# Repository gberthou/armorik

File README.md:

# ARMorik

This project proposes a simple platform that interfaces an ARM-based micro-controller (ATSAMS70, Cortex-M7-based) and non-volatile ferroelectric memory,
as an alternative to TI's MSP430FR series.

Industry lacks micro-controllers equipped with non-volatile RAM (NVRAM).
The only existing micro-controllers equipped with NVRAM have small RAM and NVRAM memories, not larger than a few kilobytes.
There is a need for micro-controllers with bigger RAM and NVRAM, implementing other architectures as well, such as ARM.

If such platforms do not exist yet, why not build one ourselves?
Here, the idea is quite simple:
take an ARM-based micro-controller which provides external pins for External Bus Interface (EBI) and which provides a Static Memory Controller (SMC).

## Hardware

- MCU: [ATSAMS70Q19](https://www.microchip.com/wwwproducts/en/ATSAMS70Q19) (ARM Cortex-M7)
- NVRAM: [FM28V202A](https://www.cypress.com/part/fm28v202a-tg) (256kB ferroelectric NVRAM)
- Socket for a [CC2500EMK](https://www.ti.com/tool/CC2500EMK) module
- [ADT7310](https://www.analog.com/en/products/adt7310.html) SPI temperature sensor
- NSL-4962 photoresistor

## Power supply

The platform is powered by a simple USB Micro-B cable.
With the onboard switch, you can choose whether you want to use the 2.2V supply or the variable supply.
The latter can be configured between 2V and 3.3V by using the onboard potentiometer.

## Programming

The platform embeds a socket for the SWD interface.
It was tested with the [Atmel ICE](https://www.microchip.com/DevelopmentTools/ProductDetails/ATATMEL-ICE) programmer.

## Code samples

My other project, [sytARM](https://gitlab.inria.fr/gabertho/sytarm), shows code and the required toolchain to make this code run on the ARMorik platform.

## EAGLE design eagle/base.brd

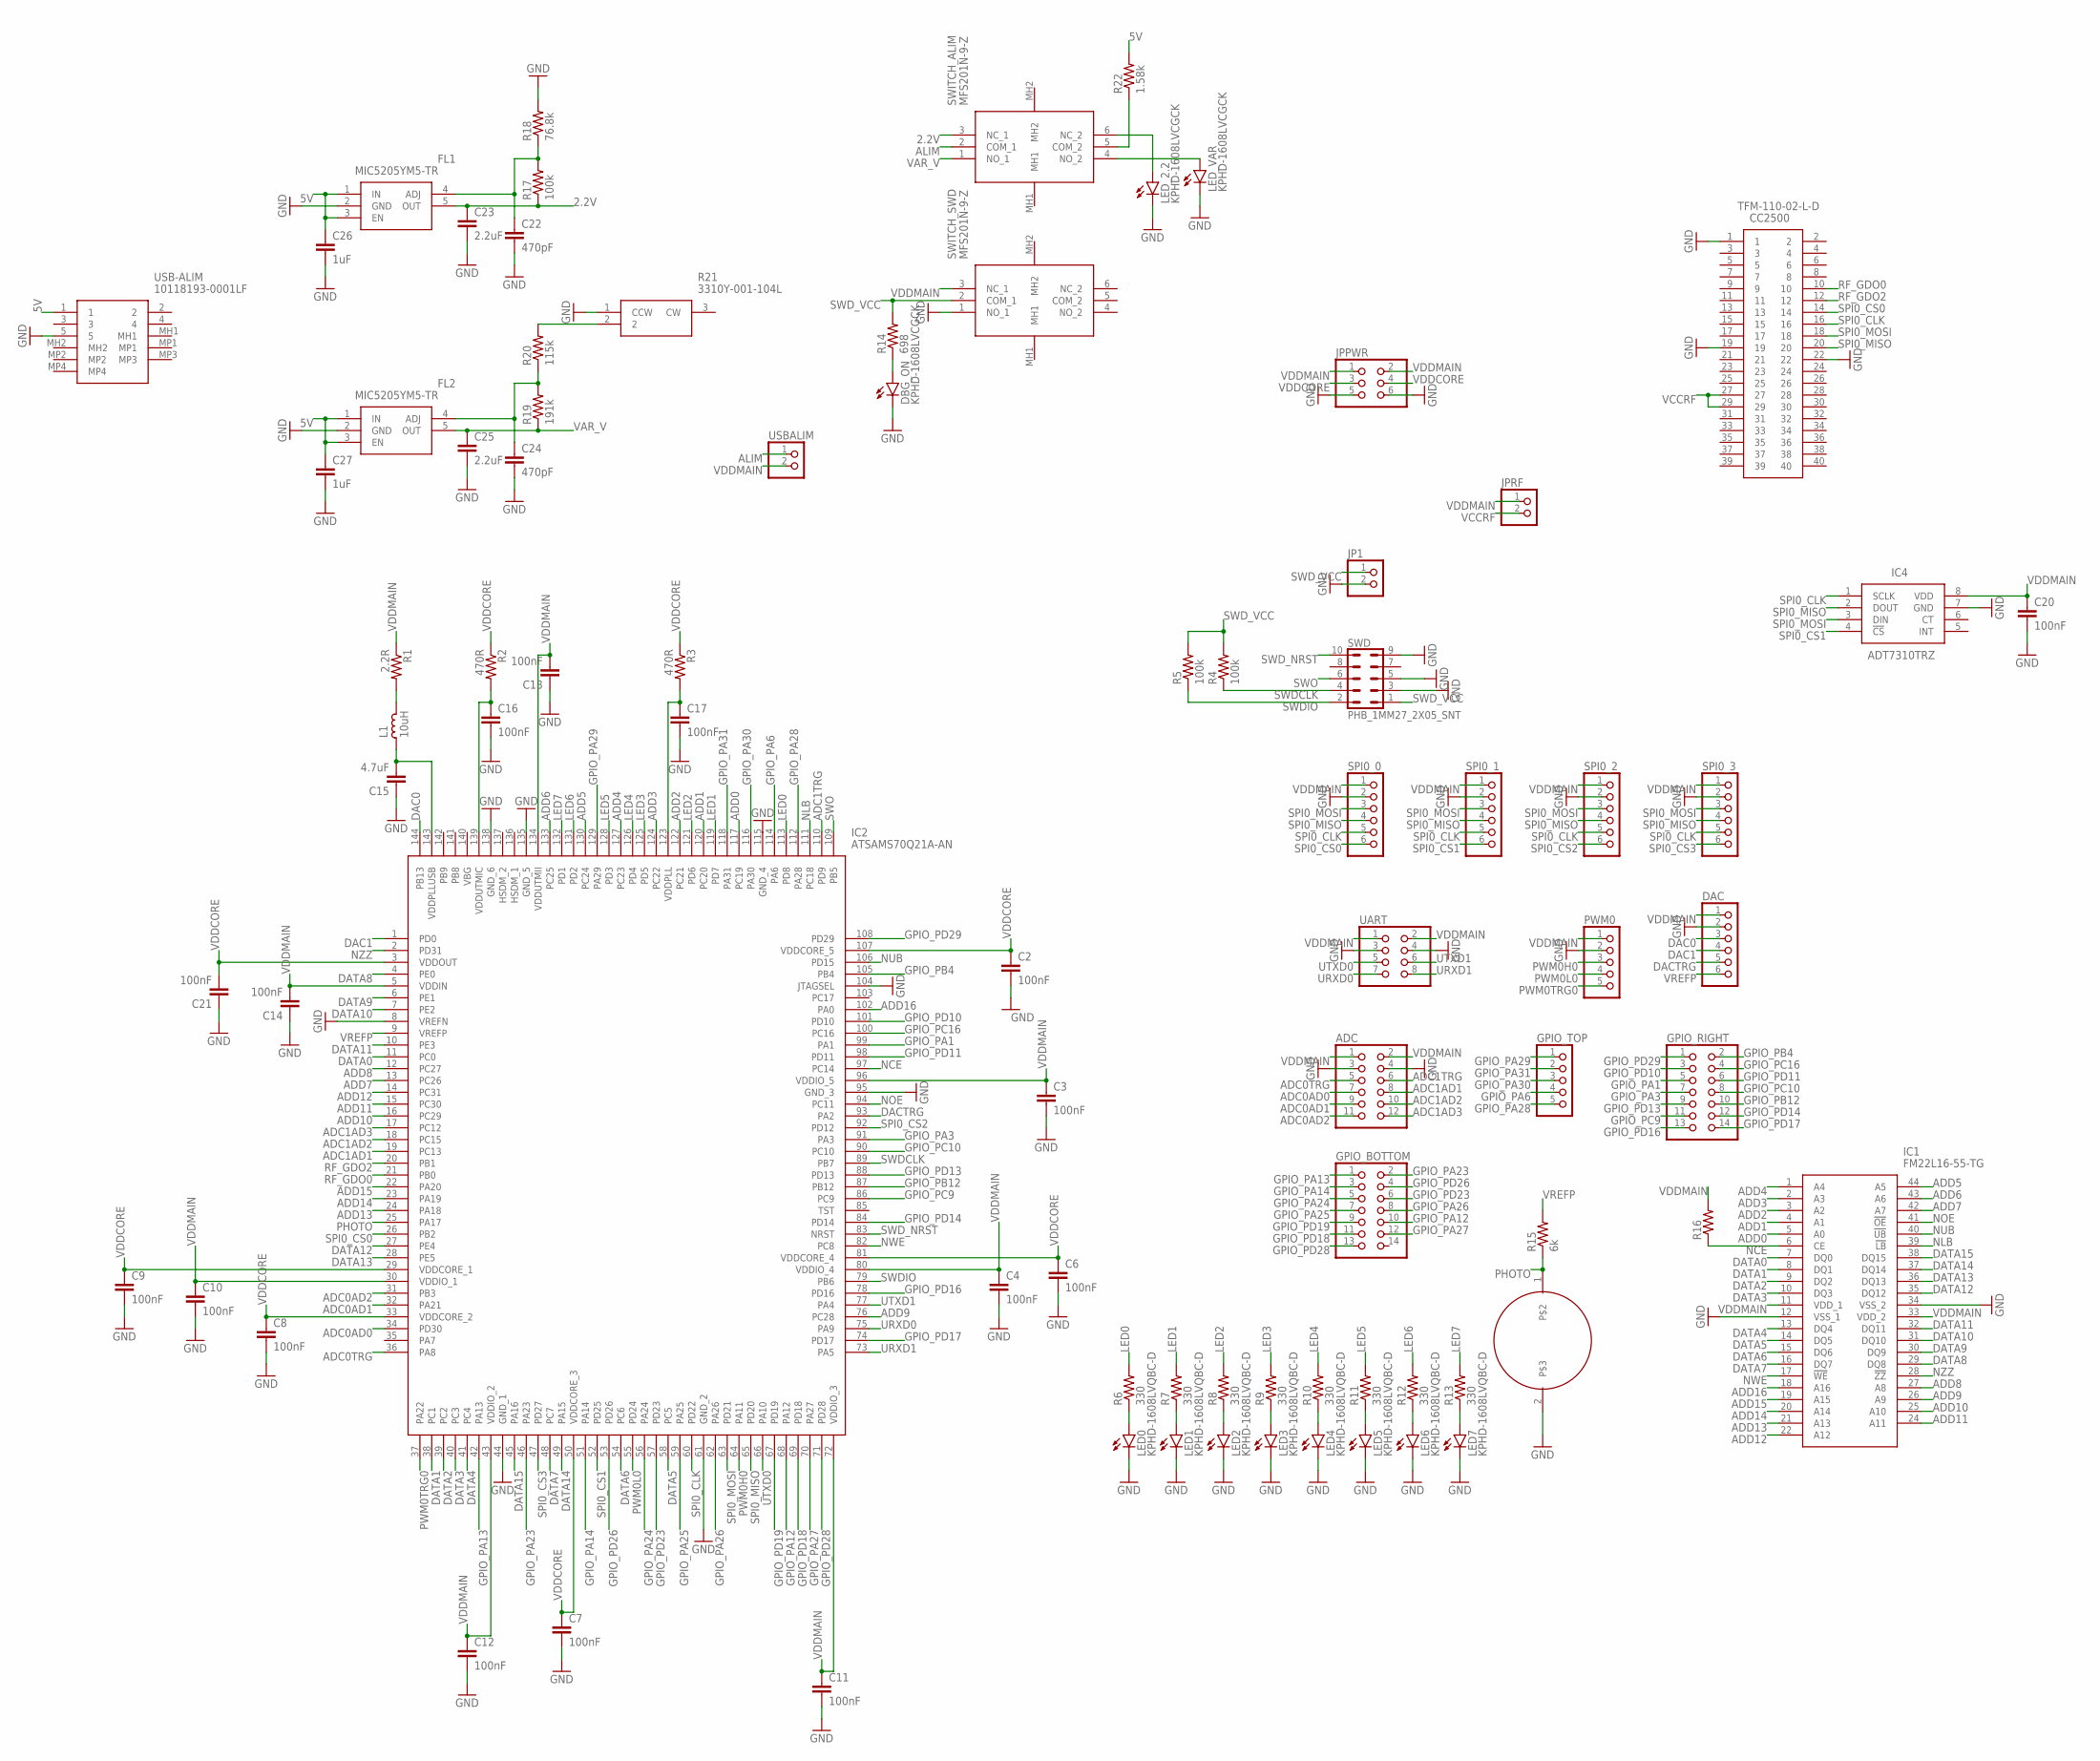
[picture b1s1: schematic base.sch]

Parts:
ADC: PINHD-2X6; 2X06
C2, C3, C4, C6, C7, C8, C9, C10, C11, C12, C13, C14, C16, C17, C20, C21: 100nF; C0603
C15: 4.7uF; C0603
C22, C24: 470pF; C0603
C23, C25: 2.2uF; C0603
C26, C27: 1uF; C0603
CC2500: TFM-110-02-L-D; TFM-110-02-L
DAC: PINHD-1X6; 1X06
DBG_ON: KPHD-1608LVCGCK; CHIP-LED0603
FL1, FL2: MIC5205YM5-TR; SOT95P280X145-5N
GPIO_BOTTOM: PINHD-2X7; 2X07
GPIO_RIGHT: PINHD-2X7; 2X07
GPIO_TOP: PINHD-1X5; 1X05
IC1: FM22L16-55-TG; SOP80P1184X119-44N
IC2: ATSAMS70Q21A-AN; QFP50P2200X2200X160-144N
IC4: ADT7310TRZ; SOIC127P600X175-8N
JP1: PINHD-1X2; 1X02
JPPWR: PINHD-2X3; 2X03
JPRF: PINHD-1X2; 1X02
L1: 10uH; L0603
LED0, LED1, LED2, LED3, LED4, LED5, LED6, LED7: KPHD-1608LVQBC-D; CHIP-LED0603
LED_2.2: KPHD-1608LVCGCK; CHIP-LED0603
LED_VAR: KPHD-1608LVCGCK; CHIP-LED0603
PWM0: PINHD-1X5; 1X05
R1: 2.2R; R0603
R2, R3: 470R; R0603
R4, R5, R17: 100k; R0603
R6, R7, R8, R9, R10, R11, R12, R13: 330; R0603
R14: 698; R0603
R15: 6k; R0603
R16: R-US_R0603; R0603
R18: 76.8k; R0603
R19: 191k; R0603
R20: 115k; R0603
R21: 3310Y-001-104L; 3310Y-001
R22: 1.58k; R0603
SPI0_0, SPI0_1, SPI0_2, SPI0_3: PINHD-1X6; 1X06
SWD: PHB_1MM27_2X05_SNT
SWITCH_ALIM: MFS201N-9-Z; MFS201N9Z
SWITCH_SWD: MFS201N-9-Z; MFS201N9Z
U$1: NSL-4962; TO-8
UART: PINHD-2X4; 2X04
USB-ALIM: 10118193-0001LF; 101181930001LF
USBALIM: PINHD-1X2; 1X02

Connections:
2.2V: C23.1, FL1.5 (OUT), R17.1, SWITCH_ALIM.3 (NC_1)
5V: C26.1, C27.1, FL1.1 (IN), FL1.3 (EN), FL2.1 (IN), FL2.3 (EN), R22.2, USB-ALIM.1
ADC0AD0: ADC.7, IC2.34 (PD30)
ADC0AD1: ADC.9, IC2.32 (PA21)
ADC0AD2: ADC.11, IC2.31 (PB3)
ADC0TRG: ADC.5, IC2.36 (PA8)
ADC1AD1: ADC.8, IC2.19 (PC13)
ADC1AD2: ADC.10, IC2.18 (PC15)
ADC1AD3: ADC.12, IC2.17 (PC12)
ADC1TRG: ADC.6, IC2.110 (PD9)
ADD0: IC1.5 (A0), IC2.117 (PC19)
ADD1: IC1.4 (A1), IC2.120 (PC20)
ADD2: IC1.3 (A2), IC2.122 (PC21)
ADD3: IC1.2 (A3), IC2.124 (PC22)
ADD4: IC1.1 (A4), IC2.127 (PC23)
ADD5: IC1.44 (A5), IC2.130 (PC24)
ADD6: IC1.43 (A6), IC2.133 (PC25)
ADD7: IC1.42 (A7), IC2.13 (PC26)
ADD8: IC1.27 (A8), IC2.12 (PC27)
ADD9: IC1.26 (A9), IC2.76 (PC28)
ADD10: IC1.25 (A10), IC2.16 (PC29)
ADD11: IC1.24 (A11), IC2.15 (PC30)
ADD12: IC1.22 (A12), IC2.14 (PC31)
ADD13: IC1.21 (A13), IC2.24 (PA18)
ADD14: IC1.20 (A14), IC2.23 (PA19)
ADD15: IC1.19 (A15), IC2.22 (PA20)
ADD16: IC1.18 (A16), IC2.102 (PA0)
ALIM: SWITCH_ALIM.2 (COM_1), USBALIM.1
DAC0: DAC.3, IC2.144 (PB13)
DAC1: DAC.4, IC2.1 (PD0)
DACTRG: DAC.5, IC2.93 (PA2)
DATA0: IC1.7 (DQ0), IC2.11 (PC0)
DATA1: IC1.8 (DQ1), IC2.38 (PC1)
DATA2: IC1.9 (DQ2), IC2.39 (PC2)
DATA3: IC1.10 (DQ3), IC2.40 (PC3)
DATA4: IC1.13 (DQ4), IC2.41 (PC4)
DATA5: IC1.14 (DQ5), IC2.58 (PC5)
DATA6: IC1.15 (DQ6), IC2.54 (PC6)
DATA7: IC1.16 (DQ7), IC2.48 (PC7)
DATA8: IC1.29 (DQ8), IC2.4 (PE0)
DATA9: IC1.30 (DQ9), IC2.6 (PE1)
DATA10: IC1.31 (DQ10), IC2.7 (PE2)
DATA11: IC1.32 (DQ11), IC2.10 (PE3)
DATA12: IC1.35 (DQ12), IC2.27 (PE4)
DATA13: IC1.36 (DQ13), IC2.28 (PE5)
DATA14: IC1.37 (DQ14), IC2.49 (PA15)
DATA15: IC1.38 (DQ15), IC2.45 (PA16)
GND: ADC.3, ADC.4, C2.2, C3.2, C4.2, C6.2, C7.2, C8.2, C9.2, C10.2, C11.2, C12.2, C13.1, C14.1, C15.1, C16.2, C17.2, C20.2, C21.1, C22.2, C23.2, C24.2, C25.2, C26.2, C27.2, CC2500.1, CC2500.19, CC2500.22, DAC.2, DBG_ON.C, FL1.2 (GND), FL2.2 (GND), IC1.12 (VSS_1), IC1.34 (VSS_2), IC2.8 (VREFN), IC2.44 (GND_1), IC2.61 (GND_2), IC2.95 (GND_3), IC2.104 (JTAGSEL), IC2.115 (GND_4), IC2.135 (GND_5), IC2.138 (GND_6), IC4.7 (GND), JP1.2, JPPWR.5, JPPWR.6, LED0.C, LED1.C, LED2.C, LED3.C, LED4.C, LED5.C, LED6.C, LED7.C, LED_2.2.C, LED_VAR.C, PWM0.2, R18.2, R21.1 (CCW), SPI0_0.2, SPI0_1.2, SPI0_2.2, SPI0_3.2, SWD.3, SWD.5, SWD.9, SWITCH_SWD.1 (NO_1), U$1.2, UART.3, UART.4, USB-ALIM.5
GPIO_PA1: GPIO_RIGHT.5, IC2.99 (PA1)
GPIO_PA3: GPIO_RIGHT.7, IC2.91 (PA3)
GPIO_PA6: GPIO_TOP.4, IC2.114 (PA6)
GPIO_PA12: GPIO_BOTTOM.10, IC2.68 (PA12)
GPIO_PA13: GPIO_BOTTOM.1, IC2.42 (PA13)
GPIO_PA14: GPIO_BOTTOM.3, IC2.51 (PA14)
GPIO_PA23: GPIO_BOTTOM.2, IC2.46 (PA23)
GPIO_PA24: GPIO_BOTTOM.5, IC2.56 (PA24)
GPIO_PA25: GPIO_BOTTOM.7, IC2.59 (PA25)
GPIO_PA26: GPIO_BOTTOM.8, IC2.62 (PA26)
GPIO_PA27: GPIO_BOTTOM.12, IC2.70 (PA27)
GPIO_PA28: GPIO_TOP.5, IC2.112 (PA28)
GPIO_PA29: GPIO_TOP.1, IC2.129 (PA29)
GPIO_PA30: GPIO_TOP.3, IC2.116 (PA30)
GPIO_PA31: GPIO_TOP.2, IC2.118 (PA31)
GPIO_PB4: GPIO_RIGHT.2, IC2.105 (PB4)
GPIO_PB12: GPIO_RIGHT.10, IC2.87 (PB12)
GPIO_PC9: GPIO_RIGHT.11, IC2.86 (PC9)
GPIO_PC10: GPIO_RIGHT.8, IC2.90 (PC10)
GPIO_PC16: GPIO_RIGHT.4, IC2.100 (PC16)
GPIO_PD10: GPIO_RIGHT.3, IC2.101 (PD10)
GPIO_PD11: GPIO_RIGHT.6, IC2.98 (PD11)
GPIO_PD13: GPIO_RIGHT.9, IC2.88 (PD13)
GPIO_PD14: GPIO_RIGHT.12, IC2.84 (PD14)
GPIO_PD16: GPIO_RIGHT.13, IC2.78 (PD16)
GPIO_PD17: GPIO_RIGHT.14, IC2.74 (PD17)
GPIO_PD18: GPIO_BOTTOM.11, IC2.69 (PD18)
GPIO_PD19: GPIO_BOTTOM.9, IC2.67 (PD19)
GPIO_PD23: GPIO_BOTTOM.6, IC2.57 (PD23)
GPIO_PD26: GPIO_BOTTOM.4, IC2.53 (PD26)
GPIO_PD28: GPIO_BOTTOM.13, IC2.71 (PD28)
GPIO_PD29: GPIO_RIGHT.1, IC2.108 (PD29)
LED0: IC2.113 (PD8), R6.2
LED1: IC2.119 (PD7), R7.2
LED2: IC2.121 (PD6), R8.2
LED3: IC2.125 (PD5), R9.2
LED4: IC2.126 (PD4), R10.2
LED5: IC2.128 (PD3), R11.2
LED6: IC2.131 (PD2), R12.2
LED7: IC2.132 (PD1), R13.2
unnamed: C15.2, IC2.143 (VDDPLLUSB), L1.2
unnamed: L1.1, R1.2
unnamed: C16.1, IC2.139 (VDDUTMIC), R2.2
unnamed: C17.1, IC2.123 (VDDPLL), R3.2
unnamed: LED0.A, R6.1
unnamed: LED1.A, R7.1
unnamed: LED2.A, R8.1
unnamed: LED3.A, R9.1
unnamed: LED4.A, R10.1
unnamed: LED5.A, R11.1
unnamed: LED6.A, R12.1
unnamed: LED7.A, R13.1
unnamed: DBG_ON.A, R14.1
unnamed: C24.1, FL2.4 (ADJ), R19.2, R20.1
unnamed: C22.1, FL1.4 (ADJ), R17.2, R18.1
unnamed: R20.2, R21.2
unnamed: LED_2.2.A, SWITCH_ALIM.6 (NC_2)
unnamed: R22.1, SWITCH_ALIM.5 (COM_2)
unnamed: LED_VAR.A, SWITCH_ALIM.4 (NO_2)
NCE: IC1.6 (CE), IC2.97 (PC14), R16.1
NLB: IC1.39 (!LB), IC2.111 (PC18)
NOE: IC1.41 (!OE), IC2.94 (PC11)
NUB: IC1.40 (!UB), IC2.106 (PD15)
NWE: IC1.17 (!WE), IC2.82 (PC8)
NZZ: IC1.28 (!ZZ), IC2.2 (PD31)
PHOTO: IC2.25 (PA17), R15.1, U$1.1
PWM0H0: IC2.64 (PA11), PWM0.3
PWM0L0: IC2.55 (PD24), PWM0.4
PWM0TRG0: IC2.37 (PA22), PWM0.5
RF_GDO0: CC2500.10, IC2.21 (PB0)
RF_GDO2: CC2500.12, IC2.20 (PB1)
SPI0_CLK: CC2500.16, IC2.60 (PD22), IC4.1 (SCLK), SPI0_0.5, SPI0_1.5, SPI0_2.5, SPI0_3.5
SPI0_CS0: CC2500.14, IC2.26 (PB2), SPI0_0.6
SPI0_CS1: IC2.52 (PD25), IC4.4 (!CS), SPI0_1.6
SPI0_CS2: IC2.92 (PD12), SPI0_2.6
SPI0_CS3: IC2.47 (PD27), SPI0_3.6
SPI0_MISO: CC2500.20, IC2.65 (PD20), IC4.2 (DOUT), SPI0_0.4, SPI0_1.4, SPI0_2.4, SPI0_3.4
SPI0_MOSI: CC2500.18, IC2.63 (PD21), IC4.3 (DIN), SPI0_0.3, SPI0_1.3, SPI0_2.3, SPI0_3.3
SWDCLK: IC2.89 (PB7), R4.1, SWD.4
SWDIO: IC2.79 (PB6), R5.1, SWD.2
SWD_NRST: IC2.83 (NRST), SWD.10
SWD_VCC: JP1.1, R4.2, R5.2, R14.2, SWD.1, SWITCH_SWD.2 (COM_1)
SWO: IC2.109 (PB5), SWD.6
URXD0: IC2.75 (PA9), UART.7
URXD1: IC2.73 (PA5), UART.8
UTXD0: IC2.66 (PA10), UART.5
UTXD1: IC2.77 (PA4), UART.6
VAR_V: C25.1, FL2.5 (OUT), R19.1, SWITCH_ALIM.1 (NO_1)
VCCRF: CC2500.27, CC2500.29, JPRF.2
VDDCORE: C2.1, C6.1, C7.1, C8.1, C9.1, C21.2, IC2.3 (VDDOUT), IC2.29 (VDDCORE_1), IC2.33 (VDDCORE_2), IC2.50 (VDDCORE_3), IC2.81 (VDDCORE_4), IC2.107 (VDDCORE_5), JPPWR.3, JPPWR.4, R2.1, R3.1
VDDMAIN: ADC.1, ADC.2, C3.1, C4.1, C10.1, C11.1, C12.1, C13.2, C14.2, C20.1, DAC.1, IC1.11 (VDD_1), IC1.33 (VDD_2), IC2.5 (VDDIN), IC2.30 (VDDIO_1), IC2.43 (VDDIO_2), IC2.72 (VDDIO_3), IC2.80 (VDDIO_4), IC2.96 (VDDIO_5), IC2.134 (VDDUTMII), IC4.8 (VDD), JPPWR.1, JPPWR.2, JPRF.1, PWM0.1, R1.1, R16.2, SPI0_0.1, SPI0_1.1, SPI0_2.1, SPI0_3.1, SWITCH_SWD.3 (NC_1), UART.1, UART.2, USBALIM.2
VREFP: DAC.6, IC2.9 (VREFP), R15.2

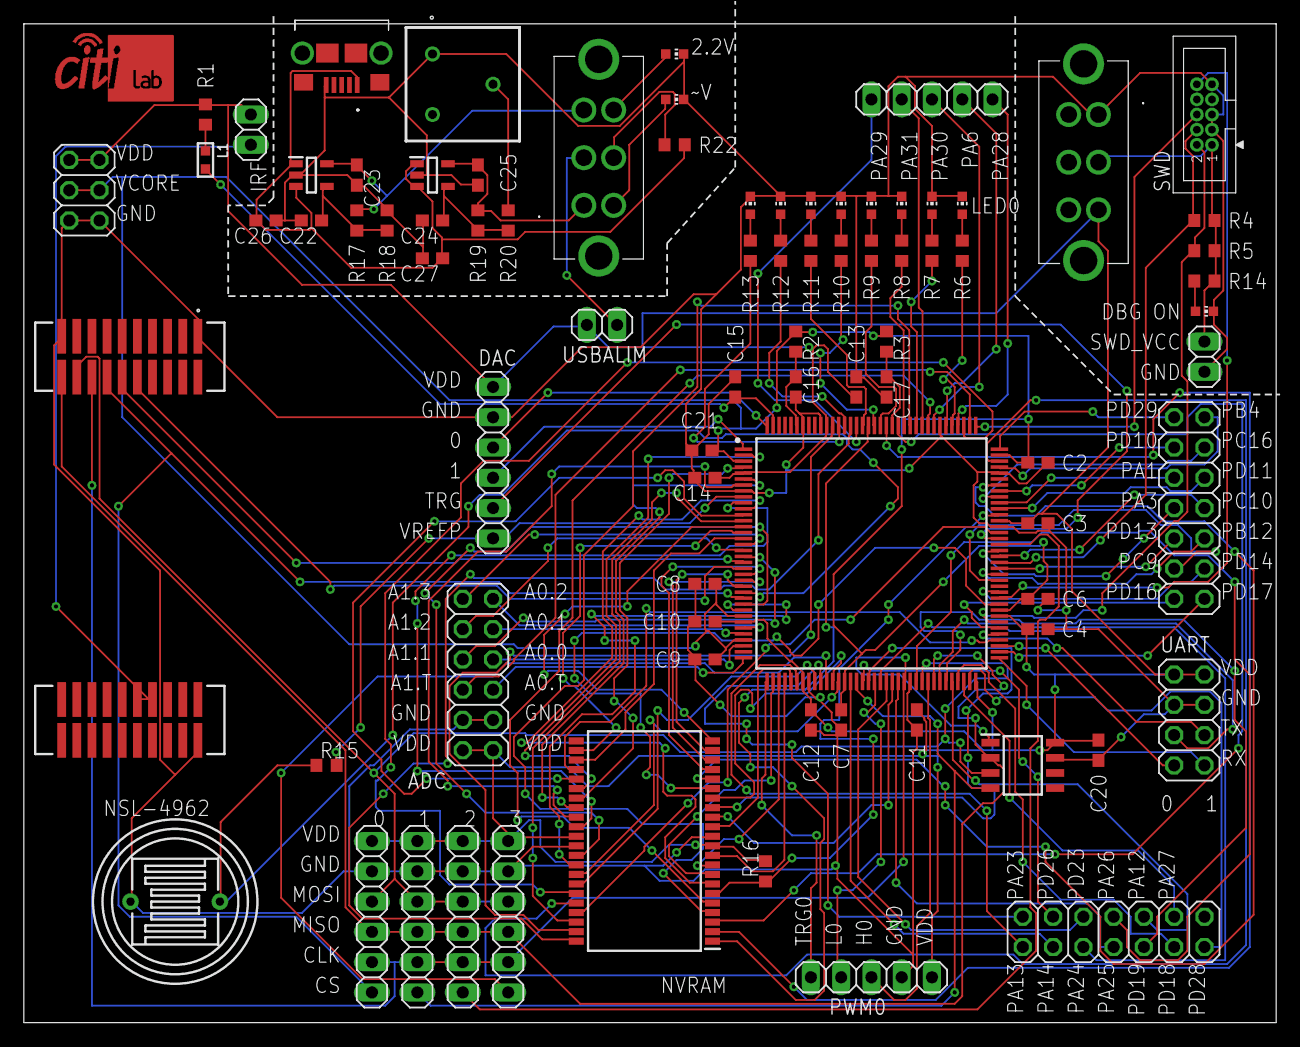
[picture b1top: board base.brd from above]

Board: 2 copper layers, 105.1 x 83.8 mm, 84 parts (0 on the bottom side), 140 nets.

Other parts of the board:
U$2: CITI_LAB_LOGO_FRONT_SMALL

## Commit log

2019-11-12 Eagle design files
2020-07-03 Update to version 2
2020-07-21 Circuit picture

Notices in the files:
parts and their libraries:
rc-master-smd: Copyright (C) 2007, Bob Starr
